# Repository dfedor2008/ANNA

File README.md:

# ANNA - High Altitude Rocket Computer

## Project Goal
Create a compact, affordable (under $100) and reliable rocket computer that can support both small and large-scale model rocket launches.

## How this project came to be
This rocket computer is part of a larger project: Moonstone. This project is a colaborative effort to launch a rocket off a High ALtitude Balloon. The link below is to slides which tell about the orgin of the project and other electronics which was done by me!!
https://docs.google.com/presentation/d/1WYTajgJSp5qMuNHan1WnkCnDspPzAP0AVPiKrxGjS5Q/edit?usp=sharing

## What is ANNA?
ANNA is a high-altitude rocket computer originally developed for a balloon-launched rocket project. It is designed to record key environmental and motion data during rocket flight, with plans to add telemetry and recovery features in future iterations.

Current features include:
- 3D orientation (gyroscope)
- Acceleration data
- Environmental measurements (temperature, pressure, humidity)
- MicroSD data logging
- Radio telemetry (in testing)

Future versions will include GPS and pyro channel support.

---

## Components

- **Microcontroller:** ATSAMD21G18A-A  
- **Radio Module:** SX1262 – Long-range, LoRa-based radio operating in the 915 MHz band  
- **Environmental Sensor:** BME280 – Measures temperature, pressure, and humidity  
- **IMU:** ICM-20948 – Provides 3D orientation and acceleration data  
- **Voltage Regulation:** AMS1117-3.3 – 3.3V linear regulator  
- **Storage:** MEM2061-01-188-00-A_REVA microSD slot

---

## Current Status *(as of 9/26/2025)*
-  Gyroscope (ICM-20948): Functional  
-  BME280 Sensor: Functional  
-  MicroSD Slot: Functional  
-  Power Regulation: Functional  
-  SX1262 Radio: Functional

---

## Features currently developed in new Board.
- **GPS Support:** For positioning and recovery  
- **Pyro Channels:** For recovery deployment and staging

---

## Radio Specification
The **SX1262** LoRa radio transmits in the 915 MHz ISM band. No HAM license is required in the U.S. to operate. So you don't need to have to pass any tests to operate it. It's inexpensive (~$3.50) and supports long-range two-way communication suitable for rocket telemetry.

---

## LED Behavior

| LED Pattern                       | Meaning                                 |
|----------------------------------|-----------------------------------------|
| Blinking 0.5s ON / 0.5s OFF      | All sensors are functioning             |
| Blinking 0.9s ON / 0.1s OFF      | At least one sensor failed to initialize |
| Off                              | Power issue / board not active          |

---

## Setting Up ANNA

1. **Download Arduino IDE:**  
   https://www.arduino.cc/en/software

2. **Install SAMD Core:**  
   https://docs.arduino.cc/learn/starting-guide/cores/

3. **Download and upload the firmware** from this repository to ANNA.

4. **Connect the board** to your computer and select *Arduino Zero (Native USB Port)* as the target board.

---

## Contact
Have questions, want to donate, or just say Hi?  
 **dawid.fedor08@gmail.com**

---
## Circut Butler 

I want to thank Circuit Butler for sponsoring my project. They have been incredibly helpful, and without their support, my project wouldn’t have been able to be completed. Their fast PCB turnaround has allowed me to quickly test and iterate, which has been crucial to the development process. Additionally, whenever I had any questions, their response time was quick and their answers were always thorough and helpful. I highly recommend Circuit Butler to anyone looking for reliable and efficient PCBs!

---

## Special Thanks

- **Max Kendall** – For design, code, and logistics support  
- **Seth Kendall** – For logistics and general support  
- **Bob Phinney** – For project funding support  
- **Szymon Fedor** – For transportation and logistical help to Sci-Tech

---

## License

This project is released under GNU GENERAL PUBLIC LICENSE and CERN Open Hardware Licence Version 2 

## Pictures:

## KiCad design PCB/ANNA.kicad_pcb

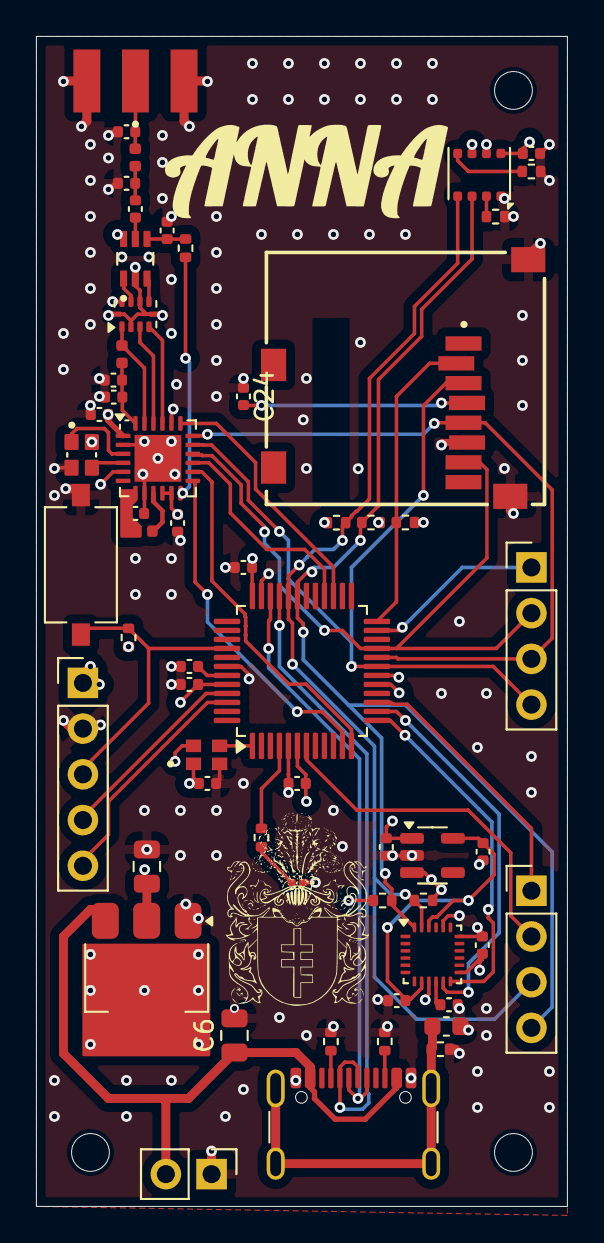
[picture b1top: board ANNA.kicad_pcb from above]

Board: 4 copper layers, 29.5 x 65.0 mm, 62 parts (0 on the bottom side), 49 nets.

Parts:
C1: 4.7 nF; C_0603_1608Metric
C2, C8, C12, C25: 1uF; C_0402_1005Metric
C3, C9, C24: 100nF; C_0402_1005Metric
C4, C26: 100 nF; C_0402_1005Metric
C5: 10 uF; C_0402_1005Metric
C6, C13: 22u; C_0805_2012Metric
C7, C15: 1nF; C_0402_1005Metric
C10: 470nF; C_0402_1005Metric
C11, C14: 47pF; C_0402_1005Metric
C17, C18, C22: 0.1uF; C_0402_1005Metric
C21: 39pF; C_0402_1005Metric
C23, C27: 3.3pF; C_0402_1005Metric
D1: LED; LED_0201_0603Metric
FL1: 0900FM15K0039; Balun_Johanson_0900FM15K0039
H1, H2, H3: MountingHole_Pad; MountingHole_2.1mm
J1: USBC; USB_C_Receptacle_GCT_USB4105-xx-A_16P_TopMnt_Horizontal
J2: PinHeader_1x05_P2.54mm_Vertical
J3: POWER IN; PinHeader_1x02_P2.54mm_Vertical
J4, J5: PinHeader_1x04_P2.54mm_Vertical
Je1: Conn_Coaxial; RFSOLUTIONS_CON-SMA-EDGE-S
Jee1: GCT_MEM2061-01-188-00-A_REVA
L1: 15uH; L_0402_1005Metric
L2: 47nH; L_0402_1005Metric
L3: 9.1nH; L_0402_1005Metric
R1, R2, R11, R12: 10k; R_0402_1005Metric
R3: 1M; R_0402_1005Metric
R4: 300; R_0402_1005Metric
R5: 220; R_0402_1005Metric
R6, R7: 5k1; R_0402_1005Metric
R8: 100; R_0402_1005Metric
R10: 1K; R_0402_1005Metric
R13, R14: 1.8k; R_0402_1005Metric
SW1: RST; SW_Tactile_SPST_NO_Straight_CK_PTS636Sx25SMTRLFS
U1: ATSAMD21G18A-A; TQFP-48_7x7mm_P0.5mm
U2: AMS1117-3.3; SOT-223-3_TabPin2
U3: SX1262IMLTRT; QFN-24-1EP_4x4mm_P0.5mm_EP2.6x2.6mm
U4: MIC5504-1.8YM5; SOT-23-5
U5: PE4259
U7: ICM-20948; InvenSense_QFN-24_3x3mm_P0.4mm
U8: BME280; Bosch_LGA-8_3x3mm_P0.8mm_ClockwisePinNumbering
U9: ECS-327TXO-2012; OSC_ECS-327TXO-2012-33-TR
Y1: FA-128_32.0000MF20X-K5; OSCCC200X160X50

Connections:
+1V8: C12.1, C17.1, U4.5 (VOUT), U7.8 (VDDIO), U7.22 (~CS)
+3.3V: C3.2, C4.1, C5.1, C7.2, C8.1, C9.1, C13.1, C18.1, C24.2, C25.1, C26.2, J2.1, Jee1.4 (VDD), R1.1, R2.1, R5.2, R10.1, R13.2, R14.1, U1.6 (VDDANA), U1.17 (VDDIO), U1.36 (VDDIO), U1.44 (VDDIN), U2.2 (VO), U3.1 (VDD_IN), U3.10 (VBAT), U3.11 (VBAT_IO), U4.1 (VIN), U4.3 (EN), U5.6 (~CTRL/~VDD), U7.13 (VDD), U8.6 (VDDIO), U8.8 (VDD), U9.1 (EN), U9.4 (VDD)
A1: J4.2, U1.7 (PB08)
BUSY: U1.12 (PA07), U3.14 (BUSY)
CS_SD: Jee1.2 (CD/DAT3), R10.2, U1.24 (PA15)
D1: J4.1, U1.15 (PA10)
D2: J5.1, U1.23 (PA14)
D+: J1.A6 (D+), J1.B6 (D+), U1.34 (PA25)
D-: J1.A7 (D-), J1.B7 (D-), U1.33 (PA24)
DIO1: U1.11 (PA06), U3.13 (DIO1)
DIO_2: R8.2, U3.12 (DIO2)
FSYNC: U1.14 (PA09), U7.11 (FSYNC)
GND: C1.1, C2.2, C3.1, C4.2, C5.2, C6.2, C7.1, C8.2, C9.2, C10.2, C11.1, C12.2, C13.2, C14.1, C15.1, C17.2, C18.2, C22.2, C23.2, C24.1, C25.2, C26.1, C27.2, D1.1 (K), FL1.2 (GND), FL1.5 (GND), FL1.7 (GND), FL1.9 (GND), FL1.10 (GND), J1.A1 (GND), J1.A12 (GND), J1.B1 (GND), J1.B12 (GND), J2.2, J3.1, Je1.2 (Ext), Jee1.6 (VSS), Jee1.11 (GND), Jee1.12 (GND), R3.2, R6.1, R7.1, R11.2, R12.2, SW1.1, U1.5 (GNDANA), U1.18 (GND), U1.35 (GND), U1.42 (GND), U2.1 (GND), U3.2 (GND), U3.5 (GND), U3.8 (GND), U3.20 (GND), U3.25 (GND), U4.2 (GND), U5.2 (GND), U7.9 (SDO/AD0), U7.18 (GND), U7.20 (GND), U8.1 (GND), U8.7 (GND), U9.2 (GND), Y1.2 (GND), Y1.4 (GND)
INT1: U1.13 (PA08), U7.12 (INT1)
MISO: J5.2, Jee1.7 (DAT0), U1.21 (PA12), U3.16 (MISO)
MOSI: J5.4, Jee1.3 (CMD), U1.19 (PB10), U3.17 (MOSI)
NSS_1: U1.27 (PA18), U3.19 (NSS)
unnamed: C21.2, C23.1, L3.1
unnamed: D1.2 (A), R4.1
unnamed: FL1.3 (RFI_N), U3.22 (RFI_N)
unnamed: FL1.4 (RFI_P), U3.21 (RFI_P)
unnamed: FL1.1 (RFO), L2.1, U3.23 (RFO)
unnamed: FL1.6 (SW_RFI), U5.3 (RF2)
unnamed: FL1.8 (SW_RFO), U5.1 (RF1)
unnamed: J1.A5 (CC1), R6.2
unnamed: J1.B5 (CC2), R7.2
unnamed: C1.2, J1.S1 (SHIELD), R3.1
unnamed: C27.1, Je1.1 (In), L3.2
unnamed: R4.2, U1.4 (PA03)
unnamed: C2.1, U1.43 (VDDCORE)
unnamed: L1.1, U3.9 (DCC_SW)
unnamed: C10.1, L1.2, U3.7 (VREG)
unnamed: C11.2, C14.2, L2.2, U3.24 (VR_PA)
unnamed: C15.2, R8.1, U5.4 (CTRL)
unnamed: C21.1, U5.5 (RFC)
unnamed: C22.1, U7.10 (REGOUT)
unnamed: R12.1, U8.2 (CSB)
unnamed: R11.1, U8.5 (SDO)
Reset: U1.28 (PA19), U3.15 (~RESET)
SCK/CLK: J5.3, Jee1.5 (CLK), U1.20 (PB11), U3.18 (SCK)
SCL: J4.3, R2.2, R14.2, U1.32 (PA23), U7.23 (SCL/SCLK), U8.4 (SCK)
SDA: J4.4, R1.2, R13.1, U1.31 (PA22), U7.24 (SDA/SDI), U8.3 (SDI)
SWCLK: J2.4, U1.45 (PA30)
SWDIO: J2.5, U1.46 (PA31)
TCXO: U1.1 (PA00), U9.3 (OUTPUT)
VBUS: C6.1, J1.A4 (VBUS), J1.A9 (VBUS), J1.B4 (VBUS), J1.B9 (VBUS), J3.2, U2.3 (VI)
XTA: U3.3 (XTA), Y1.1 (IN)
XTB: U3.4 (XTB), Y1.3 (OUT)
nRST: J2.3, R5.1, SW1.2, U1.40 (~RESET)

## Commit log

2025-07-02 Rename ANNA_Code.ino to Code/main.h
2025-08-03 Create GNU GENERAL PUBLIC LICENSE
2025-08-03 Create Hardware License
2025-08-03 Rename GNU GENERAL PUBLIC LICENSE to Software License
2025-08-19 Create Acceleration_Altitude
2025-08-19 Create Instructions_ to_view
2025-11-04 Enhance instructions with launch data context
    Added context about the data recorded during the rocket launch.
2025-11-04 Rename acceleration_raw (4).html to Acceleration_raw (4).html
2025-11-04 Update instruction to specify HTML file download
2025-11-29 Revise current status and planned features in README
    Updated the current status and features in the README.
